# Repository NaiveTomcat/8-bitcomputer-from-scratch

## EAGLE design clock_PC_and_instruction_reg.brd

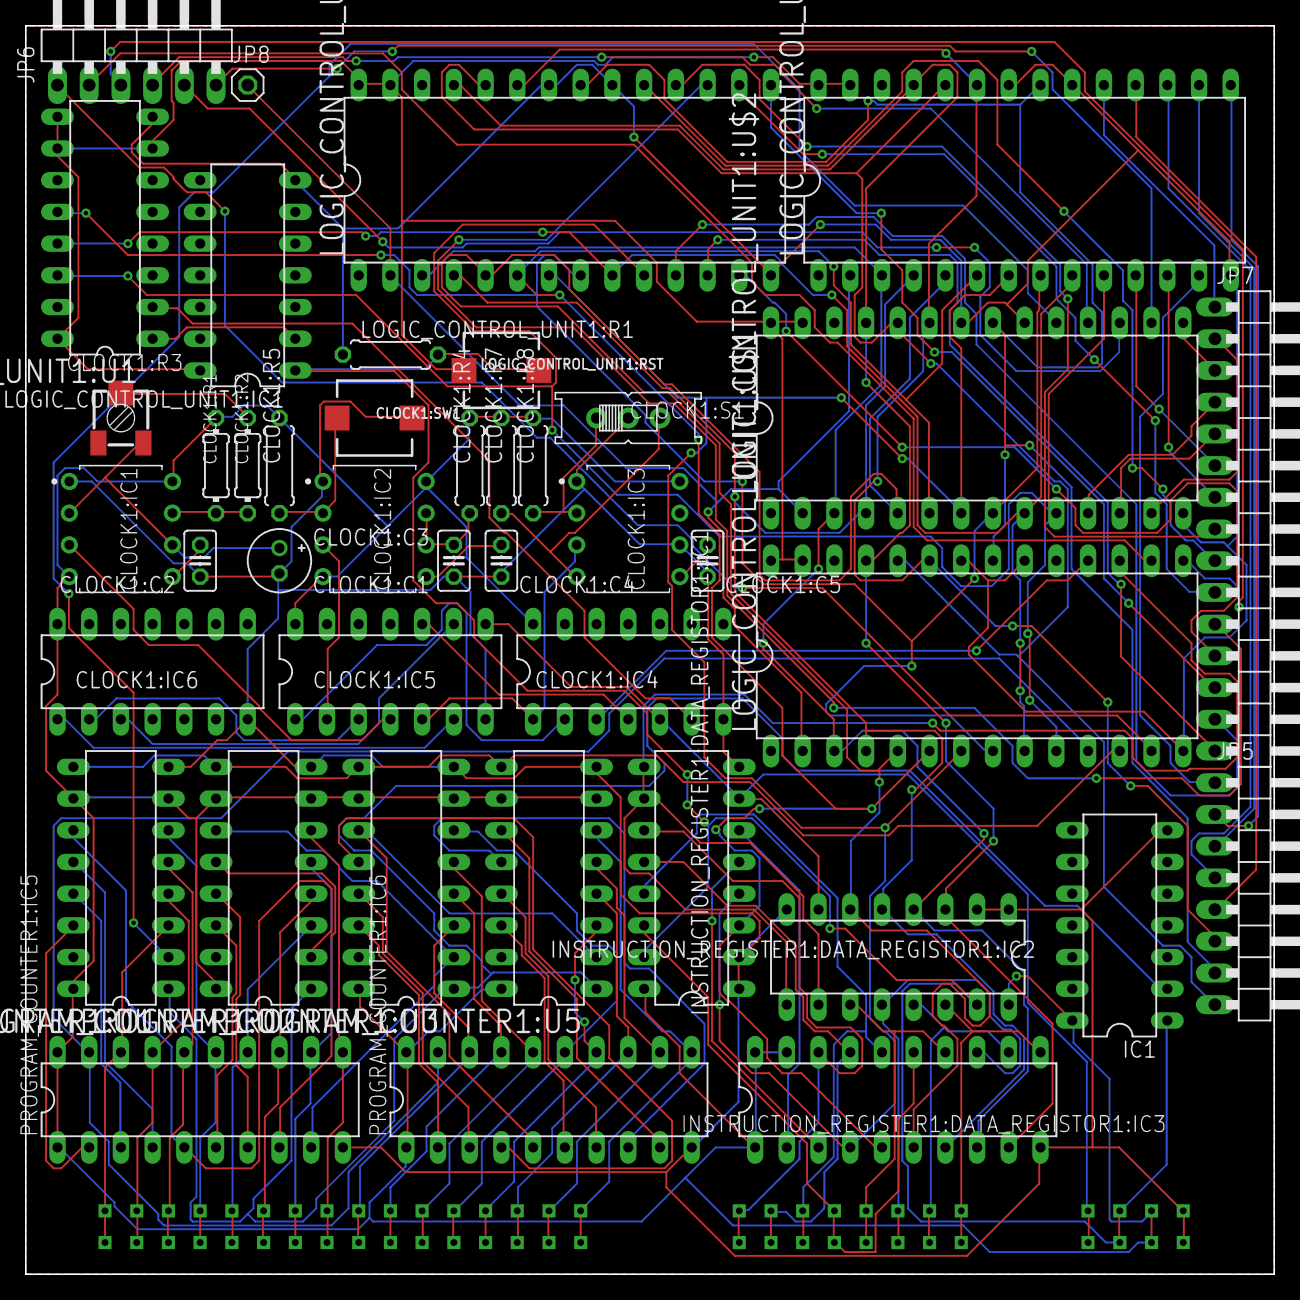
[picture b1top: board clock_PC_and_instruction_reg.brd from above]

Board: 2 copper layers, 100.0 x 100.0 mm, 43 parts (0 on the bottom side), 113 nets.

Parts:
CLOCK1:C1: 1uF; E2-5
CLOCK1:C2, CLOCK1:C4, CLOCK1:C5: 0.01uF; C025-025X050
CLOCK1:C3: 0.1uF; C025-025X050
CLOCK1:IC1, CLOCK1:IC2, CLOCK1:IC3: NE555_DIP; DIP826W53P254L959H508Q8B
CLOCK1:IC4: 74LS04N; DIL14
CLOCK1:IC5: 74LS08N; DIL14
CLOCK1:IC6: 74LS32N; DIL14
CLOCK1:R1, CLOCK1:R2: 1k; 0204/7
CLOCK1:R3: 1M; RTRIM3314J
CLOCK1:R4, CLOCK1:R7, CLOCK1:R8: 1M; 0207/7
CLOCK1:R5: 1k; 0207/7
CLOCK1:S1: EG1218
CLOCK1:SW1: PUSHBUTTON_SMD_SJ
IC1: 74LS04N; DIL14
INSTRUCTION_REGISTER1:DATA_REGISTOR1:IC1, INSTRUCTION_REGISTER1:DATA_REGISTOR1:IC2: 74LS173N; DIL16
INSTRUCTION_REGISTER1:DATA_REGISTOR1:IC3: 74LS245N; DIL20
JP5: 1X08/90
JP6: 1X06/90
JP7: 1X15/90
JP8: 1X01
LOGIC_CONTROL_UNIT1:IC1: 74LS04N; DIL14
LOGIC_CONTROL_UNIT1:R1: 1M; 0207/7
LOGIC_CONTROL_UNIT1:RST: PUSHBUTTON_SMD_SJ
LOGIC_CONTROL_UNIT1:U1: 74LS161N; DIL16
LOGIC_CONTROL_UNIT1:U$1, LOGIC_CONTROL_UNIT1:U$2, LOGIC_CONTROL_UNIT1:U$3, LOGIC_CONTROL_UNIT1:U$4: AT28C256-28DIP; DIL28-6
PROGRAM_COUNTER1:IC5, PROGRAM_COUNTER1:IC6: 74LS245N; DIL20
PROGRAM_COUNTER1:U1, PROGRAM_COUNTER1:U2, PROGRAM_COUNTER1:U3, PROGRAM_COUNTER1:U5: 74LS161N; DIL16
U$1: PORT_BOARD; PORT_FOOTPT

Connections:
!II: INSTRUCTION_REGISTER1:DATA_REGISTOR1:IC1.9, INSTRUCTION_REGISTER1:DATA_REGISTOR1:IC1.10, INSTRUCTION_REGISTER1:DATA_REGISTOR1:IC2.9, INSTRUCTION_REGISTER1:DATA_REGISTOR1:IC2.10, LOGIC_CONTROL_UNIT1:U$1.17
!PCL: LOGIC_CONTROL_UNIT1:U$1.12, PROGRAM_COUNTER1:U1.9, PROGRAM_COUNTER1:U2.9, PROGRAM_COUNTER1:U3.9, PROGRAM_COUNTER1:U5.9
!PCO: LOGIC_CONTROL_UNIT1:U$1.11, PROGRAM_COUNTER1:IC5.19, PROGRAM_COUNTER1:IC6.19
ADD: JP5.1, LOGIC_CONTROL_UNIT1:U$3.13
AI: JP7.15, LOGIC_CONTROL_UNIT1:U$4.12
AND: JP5.3, LOGIC_CONTROL_UNIT1:U$3.16
AO: JP7.14, LOGIC_CONTROL_UNIT1:U$4.11
BI: JP7.13, LOGIC_CONTROL_UNIT1:U$4.15
BO: JP7.12, LOGIC_CONTROL_UNIT1:U$4.13
CF: JP5.6, LOGIC_CONTROL_UNIT1:U$1.23, LOGIC_CONTROL_UNIT1:U$2.23, LOGIC_CONTROL_UNIT1:U$3.23, LOGIC_CONTROL_UNIT1:U$4.23
CI: JP7.11, LOGIC_CONTROL_UNIT1:U$4.17
CLOCK1:N$1: CLOCK1:IC1.7, CLOCK1:R1.1, CLOCK1:R2.2
CLOCK1:N$2: CLOCK1:R2.1, CLOCK1:R3.2
CLOCK1:N$3: CLOCK1:C1.+, CLOCK1:IC1.2, CLOCK1:IC1.6, CLOCK1:R3.1
CLOCK1:N$4: CLOCK1:C3.1, CLOCK1:IC2.6, CLOCK1:IC2.7, CLOCK1:R4.1
CLOCK1:N$5: CLOCK1:C2.1, CLOCK1:IC1.5
CLOCK1:N$6: CLOCK1:IC1.3, CLOCK1:IC5.4
CLOCK1:N$7: CLOCK1:IC4.2, CLOCK1:IC5.1
CLOCK1:N$8: CLOCK1:IC2.3, CLOCK1:IC5.2
CLOCK1:N$9: CLOCK1:IC3.3, CLOCK1:IC4.1, CLOCK1:IC5.5
CLOCK1:N$10: CLOCK1:IC5.6, CLOCK1:IC6.1
CLOCK1:N$11: CLOCK1:IC5.3, CLOCK1:IC6.2
CLOCK1:N$12: CLOCK1:IC4.4, CLOCK1:IC5.10
CLOCK1:N$13: CLOCK1:IC5.9, CLOCK1:IC6.3
CLOCK1:N$14: CLOCK1:C4.1, CLOCK1:IC2.5
CLOCK1:N$15: CLOCK1:IC2.2, CLOCK1:R5.1, CLOCK1:SW1.P$2
CLOCK1:N$17: CLOCK1:IC3.2, CLOCK1:R8.1, CLOCK1:S1.O
CLOCK1:N$18: CLOCK1:IC3.4, CLOCK1:R7.1, CLOCK1:S1.S
CLOCK1:N$19: CLOCK1:C5.1, CLOCK1:IC3.5
CO: JP7.10, LOGIC_CONTROL_UNIT1:U$4.16
D2A_HI_IN: JP6.6, LOGIC_CONTROL_UNIT1:U$2.16
D2A_LO_IN: JP6.5, LOGIC_CONTROL_UNIT1:U$2.17
D2A_OUT: JP6.4, LOGIC_CONTROL_UNIT1:U$2.18
DI: JP7.9, LOGIC_CONTROL_UNIT1:U$4.19
DO: JP7.8, LOGIC_CONTROL_UNIT1:U$4.18
EI: JP7.7, LOGIC_CONTROL_UNIT1:U$3.12
EO: JP7.6, LOGIC_CONTROL_UNIT1:U$3.11
GND: CLOCK1:C1.-, CLOCK1:C2.2, CLOCK1:C3.2, CLOCK1:C4.2, CLOCK1:C5.2, CLOCK1:IC1.1, CLOCK1:IC2.1, CLOCK1:IC3.1, CLOCK1:IC3.6, CLOCK1:IC4.7, CLOCK1:IC5.7, CLOCK1:IC6.7, CLOCK1:S1.P, CLOCK1:SW1.P$1, IC1.7, INSTRUCTION_REGISTER1:DATA_REGISTOR1:IC1.1, INSTRUCTION_REGISTER1:DATA_REGISTOR1:IC1.2, INSTRUCTION_REGISTER1:DATA_REGISTOR1:IC1.8, INSTRUCTION_REGISTER1:DATA_REGISTOR1:IC2.1, INSTRUCTION_REGISTER1:DATA_REGISTOR1:IC2.2, INSTRUCTION_REGISTER1:DATA_REGISTOR1:IC2.8, INSTRUCTION_REGISTER1:DATA_REGISTOR1:IC3.10, PROGRAM_COUNTER1:IC5.10, PROGRAM_COUNTER1:IC6.10, PROGRAM_COUNTER1:U1.8, PROGRAM_COUNTER1:U2.8, PROGRAM_COUNTER1:U3.8, PROGRAM_COUNTER1:U5.8, U$1.GND, U$1.GND1
HALT: CLOCK1:IC4.3, LOGIC_CONTROL_UNIT1:U$1.18
HI: JP7.5, LOGIC_CONTROL_UNIT1:U$2.12
HL_TO_ADDR: JP7.1, LOGIC_CONTROL_UNIT1:U$3.19
HO: JP7.4, LOGIC_CONTROL_UNIT1:U$2.11
IRO0: INSTRUCTION_REGISTER1:DATA_REGISTOR1:IC1.6, INSTRUCTION_REGISTER1:DATA_REGISTOR1:IC3.2
IRO7: INSTRUCTION_REGISTER1:DATA_REGISTOR1:IC2.3, INSTRUCTION_REGISTER1:DATA_REGISTOR1:IC3.9, LOGIC_CONTROL_UNIT1:U$1.25, LOGIC_CONTROL_UNIT1:U$2.25, LOGIC_CONTROL_UNIT1:U$3.25, LOGIC_CONTROL_UNIT1:U$4.25
LI: JP7.3, LOGIC_CONTROL_UNIT1:U$2.15
LO: JP7.2, LOGIC_CONTROL_UNIT1:U$2.13
LOGIC_CONTROL_UNIT1:GND: LOGIC_CONTROL_UNIT1:IC1.7, LOGIC_CONTROL_UNIT1:R1.1, LOGIC_CONTROL_UNIT1:U1.8, LOGIC_CONTROL_UNIT1:U$1.14, LOGIC_CONTROL_UNIT1:U$1.20, LOGIC_CONTROL_UNIT1:U$1.22, LOGIC_CONTROL_UNIT1:U$2.14, LOGIC_CONTROL_UNIT1:U$2.20, LOGIC_CONTROL_UNIT1:U$2.22, LOGIC_CONTROL_UNIT1:U$3.14, LOGIC_CONTROL_UNIT1:U$3.20, LOGIC_CONTROL_UNIT1:U$3.22, LOGIC_CONTROL_UNIT1:U$4.14, LOGIC_CONTROL_UNIT1:U$4.20, LOGIC_CONTROL_UNIT1:U$4.22
LOGIC_CONTROL_UNIT1:N$1: LOGIC_CONTROL_UNIT1:U1.14, LOGIC_CONTROL_UNIT1:U$1.10, LOGIC_CONTROL_UNIT1:U$2.10, LOGIC_CONTROL_UNIT1:U$3.10, LOGIC_CONTROL_UNIT1:U$4.10
LOGIC_CONTROL_UNIT1:N$2: LOGIC_CONTROL_UNIT1:IC1.2, LOGIC_CONTROL_UNIT1:U1.1
LOGIC_CONTROL_UNIT1:N$10: LOGIC_CONTROL_UNIT1:U1.13, LOGIC_CONTROL_UNIT1:U$1.9, LOGIC_CONTROL_UNIT1:U$2.9, LOGIC_CONTROL_UNIT1:U$3.9, LOGIC_CONTROL_UNIT1:U$4.9
LOGIC_CONTROL_UNIT1:N$11: LOGIC_CONTROL_UNIT1:U1.12, LOGIC_CONTROL_UNIT1:U$1.8, LOGIC_CONTROL_UNIT1:U$2.8, LOGIC_CONTROL_UNIT1:U$3.8, LOGIC_CONTROL_UNIT1:U$4.8
LOGIC_CONTROL_UNIT1:VCC: LOGIC_CONTROL_UNIT1:IC1.14, LOGIC_CONTROL_UNIT1:RST.P$2, LOGIC_CONTROL_UNIT1:U1.7, LOGIC_CONTROL_UNIT1:U1.9, LOGIC_CONTROL_UNIT1:U1.10, LOGIC_CONTROL_UNIT1:U1.16, LOGIC_CONTROL_UNIT1:U$1.27, LOGIC_CONTROL_UNIT1:U$1.28, LOGIC_CONTROL_UNIT1:U$2.27, LOGIC_CONTROL_UNIT1:U$2.28, LOGIC_CONTROL_UNIT1:U$3.27, LOGIC_CONTROL_UNIT1:U$3.28, LOGIC_CONTROL_UNIT1:U$4.27, LOGIC_CONTROL_UNIT1:U$4.28
MAR_IN: JP6.1, LOGIC_CONTROL_UNIT1:U$1.13
M_READ: JP6.2, LOGIC_CONTROL_UNIT1:U$1.16
M_WRITE: JP6.3, LOGIC_CONTROL_UNIT1:U$1.15
unnamed: PROGRAM_COUNTER1:IC6.11, PROGRAM_COUNTER1:U5.6, U$1.A15, U$1.A31
unnamed: PROGRAM_COUNTER1:IC6.12, PROGRAM_COUNTER1:U5.5, U$1.A14, U$1.A30
unnamed: PROGRAM_COUNTER1:IC6.13, PROGRAM_COUNTER1:U5.4, U$1.A13, U$1.A29
unnamed: PROGRAM_COUNTER1:IC6.14, PROGRAM_COUNTER1:U5.3, U$1.A12, U$1.A28
unnamed: PROGRAM_COUNTER1:IC6.15, PROGRAM_COUNTER1:U3.6, U$1.A11, U$1.A27
unnamed: PROGRAM_COUNTER1:IC6.16, PROGRAM_COUNTER1:U3.5, U$1.A10, U$1.A26
unnamed: PROGRAM_COUNTER1:IC6.17, PROGRAM_COUNTER1:U3.4, U$1.A9, U$1.A25
unnamed: PROGRAM_COUNTER1:IC6.18, PROGRAM_COUNTER1:U3.3, U$1.A8, U$1.A24
unnamed: PROGRAM_COUNTER1:IC5.11, PROGRAM_COUNTER1:U2.6, U$1.A7, U$1.A23
unnamed: PROGRAM_COUNTER1:IC5.12, PROGRAM_COUNTER1:U2.5, U$1.A6, U$1.A22
unnamed: PROGRAM_COUNTER1:IC5.13, PROGRAM_COUNTER1:U2.4, U$1.A5, U$1.A21
unnamed: PROGRAM_COUNTER1:IC5.14, PROGRAM_COUNTER1:U2.3, U$1.A4, U$1.A20
unnamed: PROGRAM_COUNTER1:IC5.15, PROGRAM_COUNTER1:U1.6, U$1.A3, U$1.A19
unnamed: PROGRAM_COUNTER1:IC5.16, PROGRAM_COUNTER1:U1.5, U$1.A2, U$1.A18
unnamed: PROGRAM_COUNTER1:IC5.17, PROGRAM_COUNTER1:U1.4, U$1.A1, U$1.A17
unnamed: PROGRAM_COUNTER1:IC5.18, PROGRAM_COUNTER1:U1.3, U$1.A0, U$1.A16
unnamed: INSTRUCTION_REGISTER1:DATA_REGISTOR1:IC1.11, INSTRUCTION_REGISTER1:DATA_REGISTOR1:IC3.18, U$1.D0, U$1.D8
unnamed: INSTRUCTION_REGISTER1:DATA_REGISTOR1:IC1.12, INSTRUCTION_REGISTER1:DATA_REGISTOR1:IC3.17, U$1.D1, U$1.D9
unnamed: INSTRUCTION_REGISTER1:DATA_REGISTOR1:IC1.13, INSTRUCTION_REGISTER1:DATA_REGISTOR1:IC3.16, U$1.D2, U$1.D10
unnamed: INSTRUCTION_REGISTER1:DATA_REGISTOR1:IC1.14, INSTRUCTION_REGISTER1:DATA_REGISTOR1:IC3.15, U$1.D3, U$1.D11
unnamed: INSTRUCTION_REGISTER1:DATA_REGISTOR1:IC2.11, INSTRUCTION_REGISTER1:DATA_REGISTOR1:IC3.14, U$1.D4, U$1.D12
unnamed: INSTRUCTION_REGISTER1:DATA_REGISTOR1:IC2.12, INSTRUCTION_REGISTER1:DATA_REGISTOR1:IC3.13, U$1.D5, U$1.D13
unnamed: INSTRUCTION_REGISTER1:DATA_REGISTOR1:IC2.13, INSTRUCTION_REGISTER1:DATA_REGISTOR1:IC3.12, U$1.D6, U$1.D14
unnamed: INSTRUCTION_REGISTER1:DATA_REGISTOR1:IC2.14, INSTRUCTION_REGISTER1:DATA_REGISTOR1:IC3.11, U$1.D7, U$1.D15
unnamed: CLOCK1:IC4.5, CLOCK1:IC5.8, INSTRUCTION_REGISTER1:DATA_REGISTOR1:IC1.7, INSTRUCTION_REGISTER1:DATA_REGISTOR1:IC2.7, U$1.CLK, U$1.CLK1
unnamed: IC1.1, INSTRUCTION_REGISTER1:DATA_REGISTOR1:IC1.15, INSTRUCTION_REGISTER1:DATA_REGISTOR1:IC2.15, LOGIC_CONTROL_UNIT1:IC1.1, LOGIC_CONTROL_UNIT1:R1.2, LOGIC_CONTROL_UNIT1:RST.P$1, U$1.RST, U$1.RST1
unnamed: IC1.2, PROGRAM_COUNTER1:U1.1, PROGRAM_COUNTER1:U2.1, PROGRAM_COUNTER1:U3.1, PROGRAM_COUNTER1:U5.1
unnamed: INSTRUCTION_REGISTER1:DATA_REGISTOR1:IC2.4, INSTRUCTION_REGISTER1:DATA_REGISTOR1:IC3.8, LOGIC_CONTROL_UNIT1:U$1.3, LOGIC_CONTROL_UNIT1:U$2.3, LOGIC_CONTROL_UNIT1:U$3.3, LOGIC_CONTROL_UNIT1:U$4.3
unnamed: INSTRUCTION_REGISTER1:DATA_REGISTOR1:IC2.5, INSTRUCTION_REGISTER1:DATA_REGISTOR1:IC3.7, LOGIC_CONTROL_UNIT1:U$1.4, LOGIC_CONTROL_UNIT1:U$2.4, LOGIC_CONTROL_UNIT1:U$3.4, LOGIC_CONTROL_UNIT1:U$4.4
unnamed: INSTRUCTION_REGISTER1:DATA_REGISTOR1:IC2.6, INSTRUCTION_REGISTER1:DATA_REGISTOR1:IC3.6, LOGIC_CONTROL_UNIT1:U$1.5, LOGIC_CONTROL_UNIT1:U$2.5, LOGIC_CONTROL_UNIT1:U$3.5, LOGIC_CONTROL_UNIT1:U$4.5
unnamed: INSTRUCTION_REGISTER1:DATA_REGISTOR1:IC1.3, INSTRUCTION_REGISTER1:DATA_REGISTOR1:IC3.5, LOGIC_CONTROL_UNIT1:U$1.6, LOGIC_CONTROL_UNIT1:U$2.6, LOGIC_CONTROL_UNIT1:U$3.6, LOGIC_CONTROL_UNIT1:U$4.6
unnamed: INSTRUCTION_REGISTER1:DATA_REGISTOR1:IC1.4, INSTRUCTION_REGISTER1:DATA_REGISTOR1:IC3.4, LOGIC_CONTROL_UNIT1:U$1.7, LOGIC_CONTROL_UNIT1:U$2.7, LOGIC_CONTROL_UNIT1:U$3.7, LOGIC_CONTROL_UNIT1:U$4.7
unnamed: INSTRUCTION_REGISTER1:DATA_REGISTOR1:IC1.5, INSTRUCTION_REGISTER1:DATA_REGISTOR1:IC3.3
unnamed: CLOCK1:IC4.6, LOGIC_CONTROL_UNIT1:U1.2
NF: JP5.7, LOGIC_CONTROL_UNIT1:U$1.21, LOGIC_CONTROL_UNIT1:U$2.21, LOGIC_CONTROL_UNIT1:U$3.21, LOGIC_CONTROL_UNIT1:U$4.21
OR: JP5.4, LOGIC_CONTROL_UNIT1:U$3.17
PC_AD: LOGIC_CONTROL_UNIT1:U$2.19, PROGRAM_COUNTER1:U1.2
PROGRAM_COUNTER1:N$2: PROGRAM_COUNTER1:IC5.5, PROGRAM_COUNTER1:U1.11, PROGRAM_COUNTER1:U2.2
PROGRAM_COUNTER1:N$3: PROGRAM_COUNTER1:IC5.9, PROGRAM_COUNTER1:U2.11, PROGRAM_COUNTER1:U3.2
PROGRAM_COUNTER1:N$4: PROGRAM_COUNTER1:IC6.5, PROGRAM_COUNTER1:U3.11, PROGRAM_COUNTER1:U5.2
PROGRAM_COUNTER1:N$23: PROGRAM_COUNTER1:IC5.2, PROGRAM_COUNTER1:U1.14
PROGRAM_COUNTER1:N$24: PROGRAM_COUNTER1:IC5.3, PROGRAM_COUNTER1:U1.13
PROGRAM_COUNTER1:N$25: PROGRAM_COUNTER1:IC5.4, PROGRAM_COUNTER1:U1.12
PROGRAM_COUNTER1:N$26: PROGRAM_COUNTER1:IC5.6, PROGRAM_COUNTER1:U2.14
PROGRAM_COUNTER1:N$27: PROGRAM_COUNTER1:IC5.7, PROGRAM_COUNTER1:U2.13
PROGRAM_COUNTER1:N$28: PROGRAM_COUNTER1:IC5.8, PROGRAM_COUNTER1:U2.12
PROGRAM_COUNTER1:N$30: PROGRAM_COUNTER1:IC6.2, PROGRAM_COUNTER1:U3.14
PROGRAM_COUNTER1:N$31: PROGRAM_COUNTER1:IC6.3, PROGRAM_COUNTER1:U3.13
PROGRAM_COUNTER1:N$32: PROGRAM_COUNTER1:IC6.4, PROGRAM_COUNTER1:U3.12
PROGRAM_COUNTER1:N$34: PROGRAM_COUNTER1:IC6.6, PROGRAM_COUNTER1:U5.14
PROGRAM_COUNTER1:N$35: PROGRAM_COUNTER1:IC6.7, PROGRAM_COUNTER1:U5.13
PROGRAM_COUNTER1:N$36: PROGRAM_COUNTER1:IC6.8, PROGRAM_COUNTER1:U5.12
PROGRAM_COUNTER1:N$37: PROGRAM_COUNTER1:IC6.9, PROGRAM_COUNTER1:U5.11
READY: JP8.1, LOGIC_CONTROL_UNIT1:U$1.2, LOGIC_CONTROL_UNIT1:U$2.2, LOGIC_CONTROL_UNIT1:U$3.2, LOGIC_CONTROL_UNIT1:U$4.2
SUB: JP5.2, LOGIC_CONTROL_UNIT1:U$3.15
VCC: CLOCK1:IC1.4, CLOCK1:IC1.8, CLOCK1:IC2.4, CLOCK1:IC2.8, CLOCK1:IC3.8, CLOCK1:IC4.14, CLOCK1:IC5.14, CLOCK1:IC6.14, CLOCK1:R1.2, CLOCK1:R4.2, CLOCK1:R5.2, CLOCK1:R7.2, CLOCK1:R8.2, IC1.14, INSTRUCTION_REGISTER1:DATA_REGISTOR1:IC1.16, INSTRUCTION_REGISTER1:DATA_REGISTOR1:IC2.16, INSTRUCTION_REGISTER1:DATA_REGISTOR1:IC3.1, INSTRUCTION_REGISTER1:DATA_REGISTOR1:IC3.19, INSTRUCTION_REGISTER1:DATA_REGISTOR1:IC3.20, PROGRAM_COUNTER1:IC5.1, PROGRAM_COUNTER1:IC5.20, PROGRAM_COUNTER1:IC6.1, PROGRAM_COUNTER1:IC6.20, PROGRAM_COUNTER1:U1.7, PROGRAM_COUNTER1:U1.10, PROGRAM_COUNTER1:U1.16, PROGRAM_COUNTER1:U2.7, PROGRAM_COUNTER1:U2.10, PROGRAM_COUNTER1:U2.16, PROGRAM_COUNTER1:U3.7, PROGRAM_COUNTER1:U3.10, PROGRAM_COUNTER1:U3.16, PROGRAM_COUNTER1:U5.7, PROGRAM_COUNTER1:U5.10, PROGRAM_COUNTER1:U5.16, U$1.VCC, U$1.VCC1
XOR: JP5.5, LOGIC_CONTROL_UNIT1:U$3.18
ZF: JP5.8, LOGIC_CONTROL_UNIT1:U$1.24, LOGIC_CONTROL_UNIT1:U$2.24, LOGIC_CONTROL_UNIT1:U$3.24, LOGIC_CONTROL_UNIT1:U$4.24

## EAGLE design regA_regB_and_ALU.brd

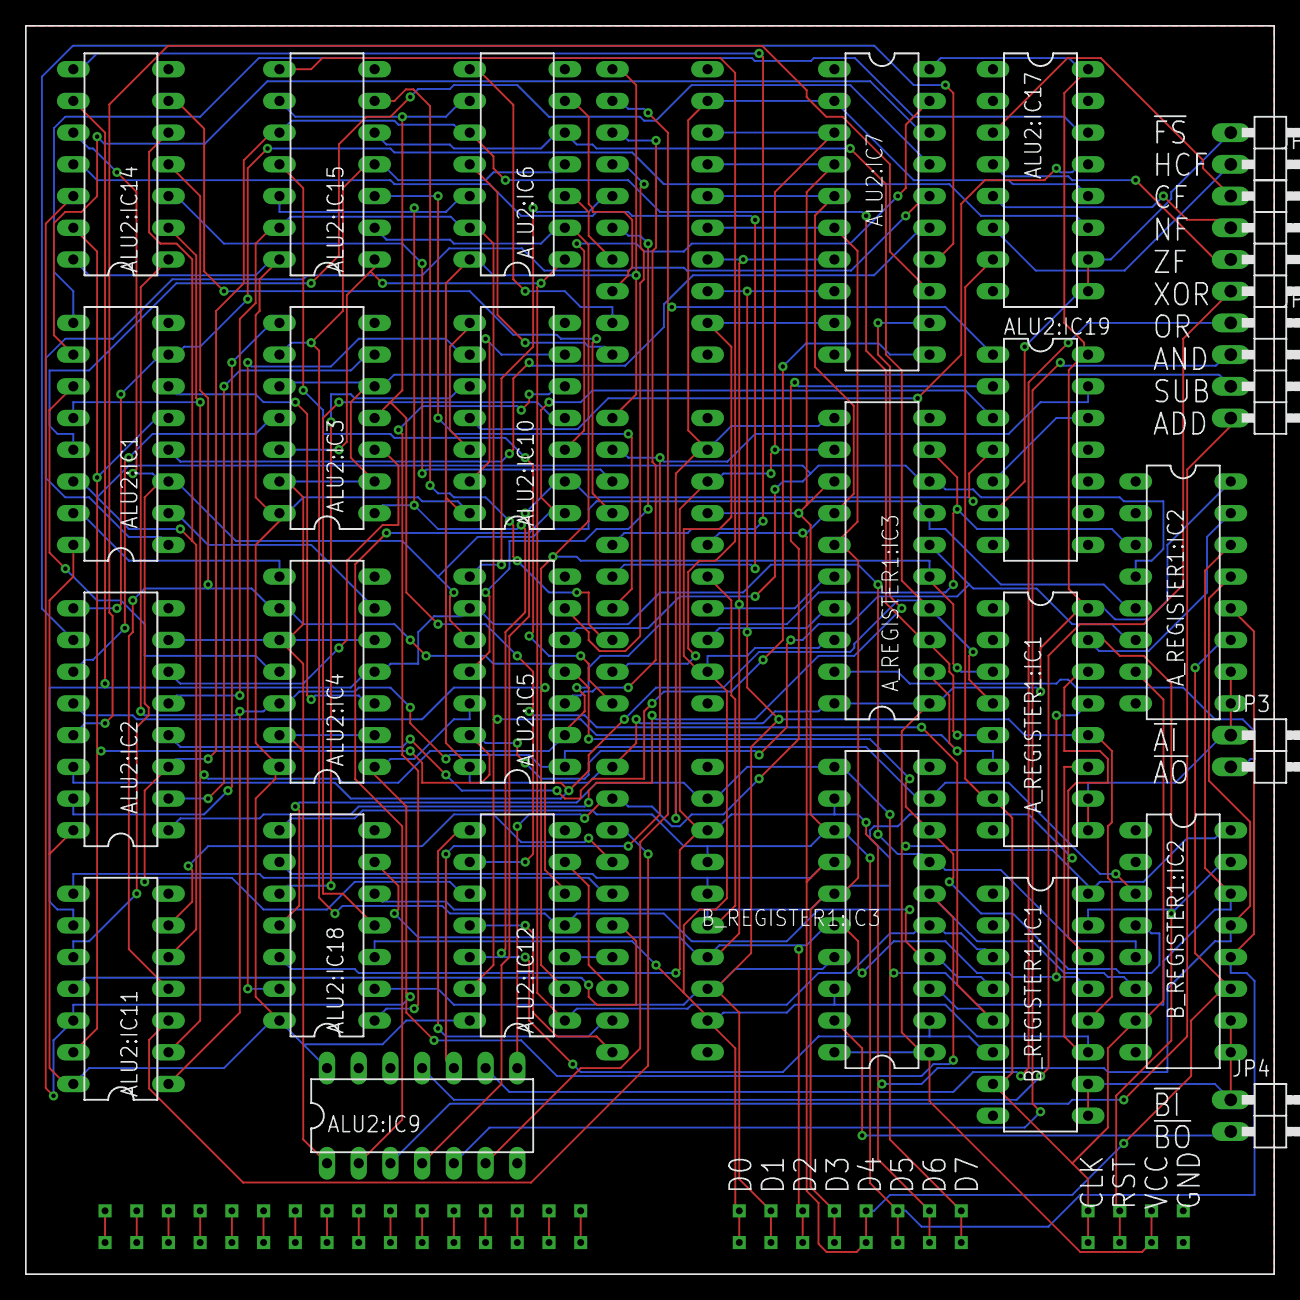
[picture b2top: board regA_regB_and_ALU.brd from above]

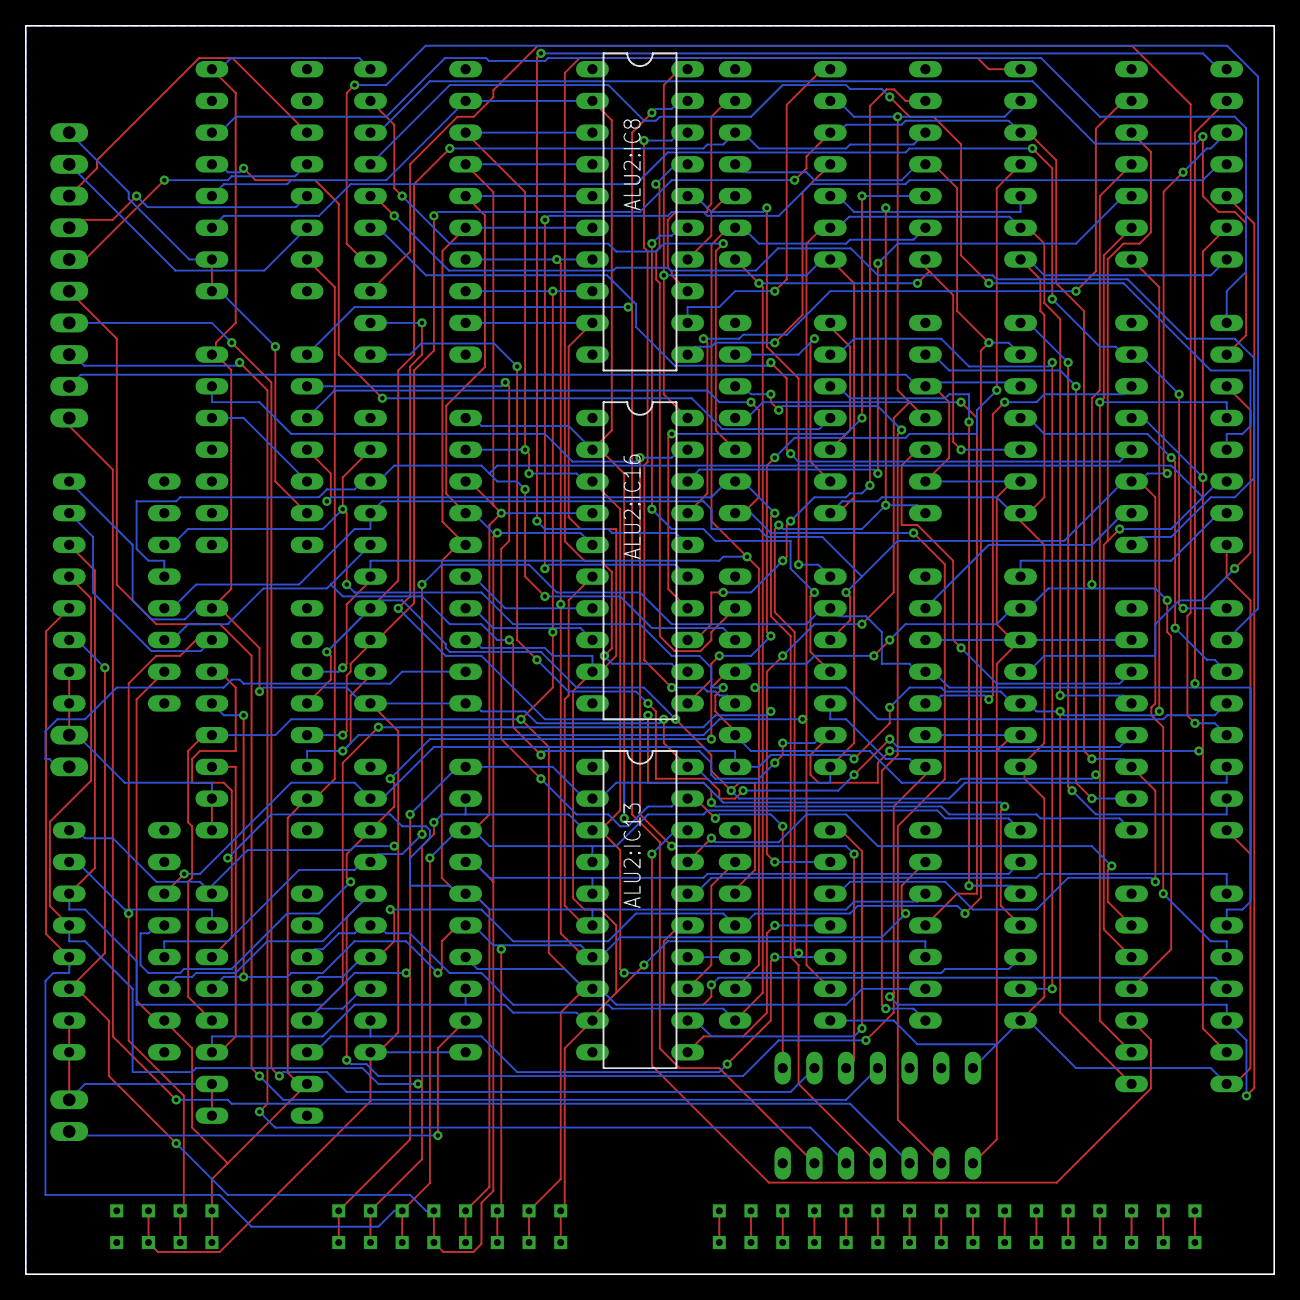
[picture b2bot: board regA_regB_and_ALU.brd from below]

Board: 2 copper layers, 100.0 x 100.0 mm, 30 parts (3 on the bottom side), 114 nets.

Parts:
ALU2:IC1, ALU2:IC2: 74LS283N; DIL16
ALU2:IC3, ALU2:IC4, ALU2:IC14, ALU2:IC15: 74LS86N; DIL14
ALU2:IC5, ALU2:IC6, ALU2:IC10: 74LS08N; DIL14
ALU2:IC7, ALU2:IC8, ALU2:IC13, ALU2:IC16: 74LS245N; DIL20
ALU2:IC9: 74LS04N; DIL14
ALU2:IC11, ALU2:IC12: 74LS32N; DIL14
ALU2:IC17: 74LS173N; DIL16
ALU2:IC18: 74LS02N; DIL14
ALU2:IC19: 74LS11N; DIL14
A_REGISTER1:IC1, A_REGISTER1:IC2: 74LS173N; DIL16
A_REGISTER1:IC3: 74LS245N; DIL20
B_REGISTER1:IC1, B_REGISTER1:IC2: 74LS173N; DIL16
B_REGISTER1:IC3: 74LS245N; DIL20
JP1: 1X08/90
JP2, JP3, JP4: 1X02/90
U$1: PORT_BOARD; PORT_FOOTPT

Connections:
!AI: A_REGISTER1:IC1.9, A_REGISTER1:IC1.10, A_REGISTER1:IC2.9, A_REGISTER1:IC2.10, JP3.1
!AO: A_REGISTER1:IC3.19, JP3.2
!BI: B_REGISTER1:IC1.9, B_REGISTER1:IC1.10, B_REGISTER1:IC2.9, B_REGISTER1:IC2.10, JP4.1
!BO: B_REGISTER1:IC3.19, JP4.2
!FS: ALU2:IC17.9, ALU2:IC17.10, ALU2:IC19.6, JP2.1
ADD: ALU2:IC9.3, JP1.8
ALU2:N$1: ALU2:IC1.7, ALU2:IC2.9, ALU2:IC17.11
ALU2:N$2: ALU2:IC2.10, ALU2:IC7.14
ALU2:N$3: ALU2:IC1.4, ALU2:IC7.15
ALU2:N$4: ALU2:IC2.4, ALU2:IC7.11
ALU2:N$5: ALU2:IC2.1, ALU2:IC7.12
ALU2:N$6: ALU2:IC2.13, ALU2:IC7.13
ALU2:N$7: ALU2:IC1.1, ALU2:IC7.16
ALU2:N$8: ALU2:IC1.13, ALU2:IC7.17
ALU2:N$9: ALU2:IC1.10, ALU2:IC7.18
ALU2:N$10: ALU2:IC2.6, ALU2:IC3.3
ALU2:N$11: ALU2:IC2.2, ALU2:IC3.6
ALU2:N$12: ALU2:IC2.15, ALU2:IC3.8
ALU2:N$13: ALU2:IC2.11, ALU2:IC3.11
ALU2:N$14: ALU2:IC1.6, ALU2:IC4.3
ALU2:N$15: ALU2:IC1.2, ALU2:IC4.6
ALU2:N$16: ALU2:IC1.15, ALU2:IC4.8
ALU2:N$17: ALU2:IC1.11, ALU2:IC4.11
ALU2:N$18: ALU2:IC5.3, ALU2:IC8.18
ALU2:N$19: ALU2:IC5.6, ALU2:IC8.17
ALU2:N$20: ALU2:IC5.8, ALU2:IC8.16
ALU2:N$21: ALU2:IC5.11, ALU2:IC8.15
ALU2:N$22: ALU2:IC6.3, ALU2:IC8.14
ALU2:N$23: ALU2:IC6.6, ALU2:IC8.13
ALU2:N$24: ALU2:IC6.8, ALU2:IC8.12
ALU2:N$25: ALU2:IC6.11, ALU2:IC8.11
ALU2:N$26: ALU2:IC9.2, ALU2:IC10.1, ALU2:IC19.3
ALU2:N$27: ALU2:IC9.4, ALU2:IC10.2, ALU2:IC19.4
ALU2:N$28: ALU2:IC7.19, ALU2:IC10.3
ALU2:N$29: ALU2:IC8.19, ALU2:IC9.6, ALU2:IC19.1
ALU2:N$30: ALU2:IC11.3, ALU2:IC13.18
ALU2:N$31: ALU2:IC14.3, ALU2:IC16.18
ALU2:N$32: ALU2:IC11.8, ALU2:IC13.16
ALU2:N$33: ALU2:IC11.11, ALU2:IC13.15
ALU2:N$34: ALU2:IC12.3, ALU2:IC13.14
ALU2:N$35: ALU2:IC12.6, ALU2:IC13.13
ALU2:N$36: ALU2:IC12.8, ALU2:IC13.12
ALU2:N$37: ALU2:IC12.11, ALU2:IC13.11
ALU2:N$38: ALU2:IC9.8, ALU2:IC13.19, ALU2:IC19.2
ALU2:N$39: ALU2:IC11.6, ALU2:IC13.17
ALU2:N$40: ALU2:IC14.6, ALU2:IC16.17
ALU2:N$41: ALU2:IC14.8, ALU2:IC16.16
ALU2:N$42: ALU2:IC14.11, ALU2:IC16.15
ALU2:N$43: ALU2:IC15.3, ALU2:IC16.14
ALU2:N$44: ALU2:IC15.6, ALU2:IC16.13
ALU2:N$45: ALU2:IC15.8, ALU2:IC16.12
ALU2:N$46: ALU2:IC15.11, ALU2:IC16.11
ALU2:N$47: ALU2:IC9.10, ALU2:IC16.19, ALU2:IC19.13
ALU2:N$48: ALU2:IC1.9, ALU2:IC17.14
ALU2:N$49: ALU2:IC10.6, ALU2:IC10.13
ALU2:N$50: ALU2:IC10.8, ALU2:IC10.12
ALU2:N$51: ALU2:IC10.5, ALU2:IC18.1
ALU2:N$52: ALU2:IC10.4, ALU2:IC18.4
ALU2:N$53: ALU2:IC10.10, ALU2:IC18.10
ALU2:N$54: ALU2:IC10.9, ALU2:IC18.13
ALU2:N$55: ALU2:IC10.11, ALU2:IC17.13
ALU2:N$56: ALU2:IC19.5, ALU2:IC19.12
AND: ALU2:IC9.5, JP1.6
CF: ALU2:IC17.3, JP1.1
CLOCK1: ALU2:IC17.7, A_REGISTER1:IC1.7, A_REGISTER1:IC2.7, B_REGISTER1:IC1.7, B_REGISTER1:IC2.7, U$1.CLK, U$1.CLK1
DATA_0: ALU2:IC7.9, ALU2:IC8.9, ALU2:IC13.9, ALU2:IC16.9, ALU2:IC18.3, A_REGISTER1:IC1.11, A_REGISTER1:IC3.18, B_REGISTER1:IC1.11, B_REGISTER1:IC3.18, U$1.D0, U$1.D8
DATA_1: ALU2:IC7.8, ALU2:IC8.8, ALU2:IC13.8, ALU2:IC16.8, ALU2:IC18.2, A_REGISTER1:IC1.12, A_REGISTER1:IC3.17, B_REGISTER1:IC1.12, B_REGISTER1:IC3.17, U$1.D1, U$1.D9
DATA_2: ALU2:IC7.7, ALU2:IC8.7, ALU2:IC13.7, ALU2:IC16.7, ALU2:IC18.6, A_REGISTER1:IC1.13, A_REGISTER1:IC3.16, B_REGISTER1:IC1.13, B_REGISTER1:IC3.16, U$1.D2, U$1.D10
DATA_3: ALU2:IC7.6, ALU2:IC8.6, ALU2:IC13.6, ALU2:IC16.6, ALU2:IC18.5, A_REGISTER1:IC1.14, A_REGISTER1:IC3.15, B_REGISTER1:IC1.14, B_REGISTER1:IC3.15, U$1.D3, U$1.D11
DATA_4: ALU2:IC7.5, ALU2:IC8.5, ALU2:IC13.5, ALU2:IC16.5, ALU2:IC18.9, A_REGISTER1:IC2.11, A_REGISTER1:IC3.14, B_REGISTER1:IC2.11, B_REGISTER1:IC3.14, U$1.D4, U$1.D12
DATA_5: ALU2:IC7.4, ALU2:IC8.4, ALU2:IC13.4, ALU2:IC16.4, ALU2:IC18.8, A_REGISTER1:IC2.12, A_REGISTER1:IC3.13, B_REGISTER1:IC2.12, B_REGISTER1:IC3.13, U$1.D5, U$1.D13
DATA_6: ALU2:IC7.3, ALU2:IC8.3, ALU2:IC13.3, ALU2:IC16.3, ALU2:IC18.12, A_REGISTER1:IC2.13, A_REGISTER1:IC3.12, B_REGISTER1:IC2.13, B_REGISTER1:IC3.12, U$1.D6, U$1.D14
DATA_7: ALU2:IC7.2, ALU2:IC8.2, ALU2:IC13.2, ALU2:IC16.2, ALU2:IC17.12, ALU2:IC18.11, A_REGISTER1:IC2.14, A_REGISTER1:IC3.11, B_REGISTER1:IC2.14, B_REGISTER1:IC3.11, U$1.D7, U$1.D15
GND: ALU2:IC1.8, ALU2:IC2.8, ALU2:IC3.7, ALU2:IC4.7, ALU2:IC5.7, ALU2:IC6.7, ALU2:IC7.1, ALU2:IC7.10, ALU2:IC8.1, ALU2:IC8.10, ALU2:IC9.7, ALU2:IC10.7, ALU2:IC11.7, ALU2:IC12.7, ALU2:IC13.1, ALU2:IC13.10, ALU2:IC14.7, ALU2:IC15.7, ALU2:IC16.1, ALU2:IC16.10, ALU2:IC17.1, ALU2:IC17.2, ALU2:IC17.8, ALU2:IC18.7, ALU2:IC19.7, A_REGISTER1:IC1.1, A_REGISTER1:IC1.2, A_REGISTER1:IC1.8, A_REGISTER1:IC2.1, A_REGISTER1:IC2.2, A_REGISTER1:IC2.8, A_REGISTER1:IC3.10, B_REGISTER1:IC1.1, B_REGISTER1:IC1.2, B_REGISTER1:IC1.8, B_REGISTER1:IC2.1, B_REGISTER1:IC2.2, B_REGISTER1:IC2.8, B_REGISTER1:IC3.10, U$1.GND, U$1.GND1
HCF: ALU2:IC17.6, JP2.2
unnamed: U$1.A15, U$1.A31
unnamed: U$1.A14, U$1.A30
unnamed: U$1.A13, U$1.A29
unnamed: U$1.A12, U$1.A28
unnamed: U$1.A11, U$1.A27
unnamed: U$1.A10, U$1.A26
unnamed: U$1.A9, U$1.A25
unnamed: U$1.A8, U$1.A24
unnamed: U$1.A7, U$1.A23
unnamed: U$1.A6, U$1.A22
unnamed: U$1.A5, U$1.A21
unnamed: U$1.A4, U$1.A20
unnamed: U$1.A3, U$1.A19
unnamed: U$1.A2, U$1.A18
unnamed: U$1.A1, U$1.A17
unnamed: U$1.A0, U$1.A16
unnamed: ALU2:IC2.5, ALU2:IC6.13, ALU2:IC12.13, ALU2:IC15.13, A_REGISTER1:IC1.6, A_REGISTER1:IC3.2
unnamed: ALU2:IC2.3, ALU2:IC6.10, ALU2:IC12.10, ALU2:IC15.10, A_REGISTER1:IC1.5, A_REGISTER1:IC3.3
unnamed: ALU2:IC2.14, ALU2:IC6.5, ALU2:IC12.5, ALU2:IC15.5, A_REGISTER1:IC1.4, A_REGISTER1:IC3.4
unnamed: ALU2:IC2.12, ALU2:IC6.2, ALU2:IC12.2, ALU2:IC15.2, A_REGISTER1:IC1.3, A_REGISTER1:IC3.5
unnamed: ALU2:IC1.5, ALU2:IC5.13, ALU2:IC11.13, ALU2:IC14.13, A_REGISTER1:IC2.6, A_REGISTER1:IC3.6
unnamed: ALU2:IC1.3, ALU2:IC5.10, ALU2:IC11.10, ALU2:IC14.10, A_REGISTER1:IC2.5, A_REGISTER1:IC3.7
unnamed: ALU2:IC1.14, ALU2:IC5.5, ALU2:IC11.5, ALU2:IC14.5, A_REGISTER1:IC2.4, A_REGISTER1:IC3.8
unnamed: ALU2:IC1.12, ALU2:IC5.2, ALU2:IC11.2, ALU2:IC14.2, A_REGISTER1:IC2.3, A_REGISTER1:IC3.9
unnamed: ALU2:IC3.1, ALU2:IC6.12, ALU2:IC12.12, ALU2:IC15.12, B_REGISTER1:IC1.6, B_REGISTER1:IC3.2
unnamed: ALU2:IC3.4, ALU2:IC6.9, ALU2:IC12.9, ALU2:IC15.9, B_REGISTER1:IC1.5, B_REGISTER1:IC3.3
unnamed: ALU2:IC3.9, ALU2:IC6.4, ALU2:IC12.4, ALU2:IC15.4, B_REGISTER1:IC1.4, B_REGISTER1:IC3.4
unnamed: ALU2:IC3.12, ALU2:IC6.1, ALU2:IC12.1, ALU2:IC15.1, B_REGISTER1:IC1.3, B_REGISTER1:IC3.5
unnamed: ALU2:IC4.1, ALU2:IC5.12, ALU2:IC11.12, ALU2:IC14.12, B_REGISTER1:IC2.6, B_REGISTER1:IC3.6
unnamed: ALU2:IC4.4, ALU2:IC5.9, ALU2:IC11.9, ALU2:IC14.9, B_REGISTER1:IC2.5, B_REGISTER1:IC3.7
unnamed: ALU2:IC4.9, ALU2:IC5.4, ALU2:IC11.4, ALU2:IC14.4, B_REGISTER1:IC2.4, B_REGISTER1:IC3.8
unnamed: ALU2:IC4.12, ALU2:IC5.1, ALU2:IC11.1, ALU2:IC14.1, B_REGISTER1:IC2.3, B_REGISTER1:IC3.9
unnamed: A_REGISTER1:IC1.15, A_REGISTER1:IC2.15, B_REGISTER1:IC1.15, B_REGISTER1:IC2.15, U$1.RST, U$1.RST1
NF: ALU2:IC17.5, JP1.2
OR: ALU2:IC9.9, JP1.5
SUB: ALU2:IC2.7, ALU2:IC3.2, ALU2:IC3.5, ALU2:IC3.10, ALU2:IC3.13, ALU2:IC4.2, ALU2:IC4.5, ALU2:IC4.10, ALU2:IC4.13, ALU2:IC9.1, JP1.7
VCC: ALU2:IC1.16, ALU2:IC2.16, ALU2:IC3.14, ALU2:IC4.14, ALU2:IC5.14, ALU2:IC6.14, ALU2:IC7.20, ALU2:IC8.20, ALU2:IC9.14, ALU2:IC10.14, ALU2:IC11.14, ALU2:IC12.14, ALU2:IC13.20, ALU2:IC14.14, ALU2:IC15.14, ALU2:IC16.20, ALU2:IC17.16, ALU2:IC18.14, ALU2:IC19.14, A_REGISTER1:IC1.16, A_REGISTER1:IC2.16, A_REGISTER1:IC3.1, A_REGISTER1:IC3.20, B_REGISTER1:IC1.16, B_REGISTER1:IC2.16, B_REGISTER1:IC3.1, B_REGISTER1:IC3.20, U$1.VCC, U$1.VCC1
XOR: ALU2:IC9.11, JP1.4
ZF: ALU2:IC17.4, JP1.3
